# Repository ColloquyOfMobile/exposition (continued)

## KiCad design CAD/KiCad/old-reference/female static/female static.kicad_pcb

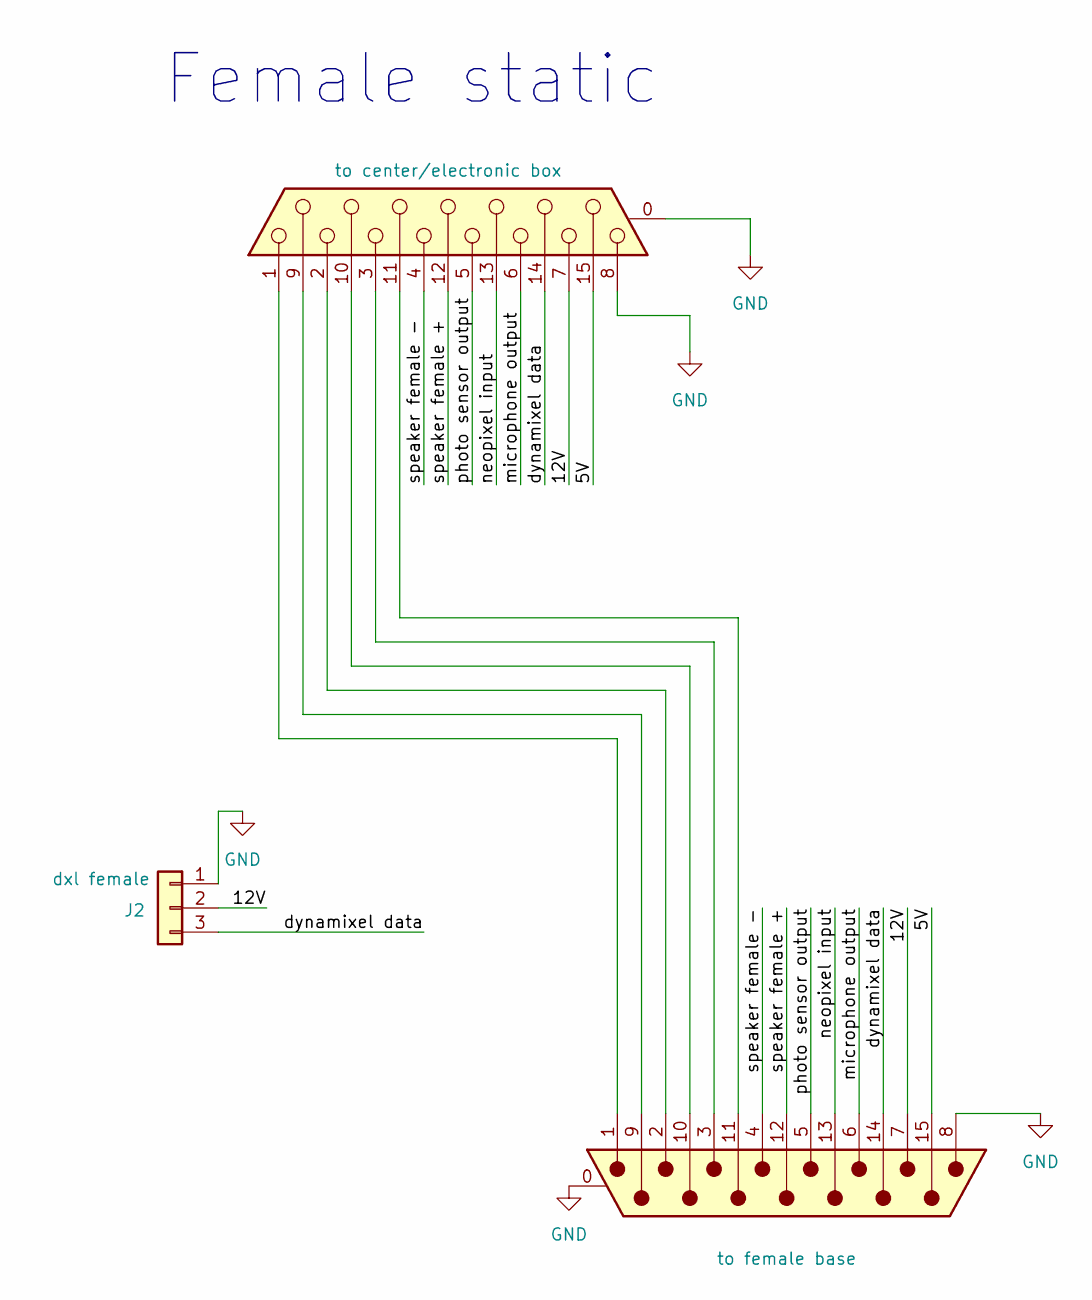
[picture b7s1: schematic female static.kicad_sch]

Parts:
J1: to center/electronic box; DSUB-15_Female_Horizontal_P2.77x2.84mm_EdgePinOffset4.94mm_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
J2: dxl female; JST_EH_B3B-EH-A_1x03_P2.50mm_Vertical
J3: to female base; DSUB-15_Male_Horizontal_P2.77x2.84mm_EdgePinOffset4.94mm_Ho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

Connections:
/5V: J1.15, J3.15
/12V: J1.7, J2.2, J3.7
/dynamixel data: J1.14, J2.3, J3.14
/microphone output: J1.6, J3.6
/neopixel input: J1.13, J3.13
/photo sensor output: J1.5, J3.5
/speaker female +: J1.12, J3.12
/speaker female -: J1.4, J3.4
GND: J1.0 (PAD), J1.8, J2.1, J3.0 (PAD), J3.8
unnamed: J1.9, J3.9
unnamed: J1.10, J3.10
unnamed: J1.11 (P111), J3.11 (P111)
unnamed: J1.1, J3.1
unnamed: J1.2, J3.2
unnamed: J1.3, J3.3

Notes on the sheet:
Female static

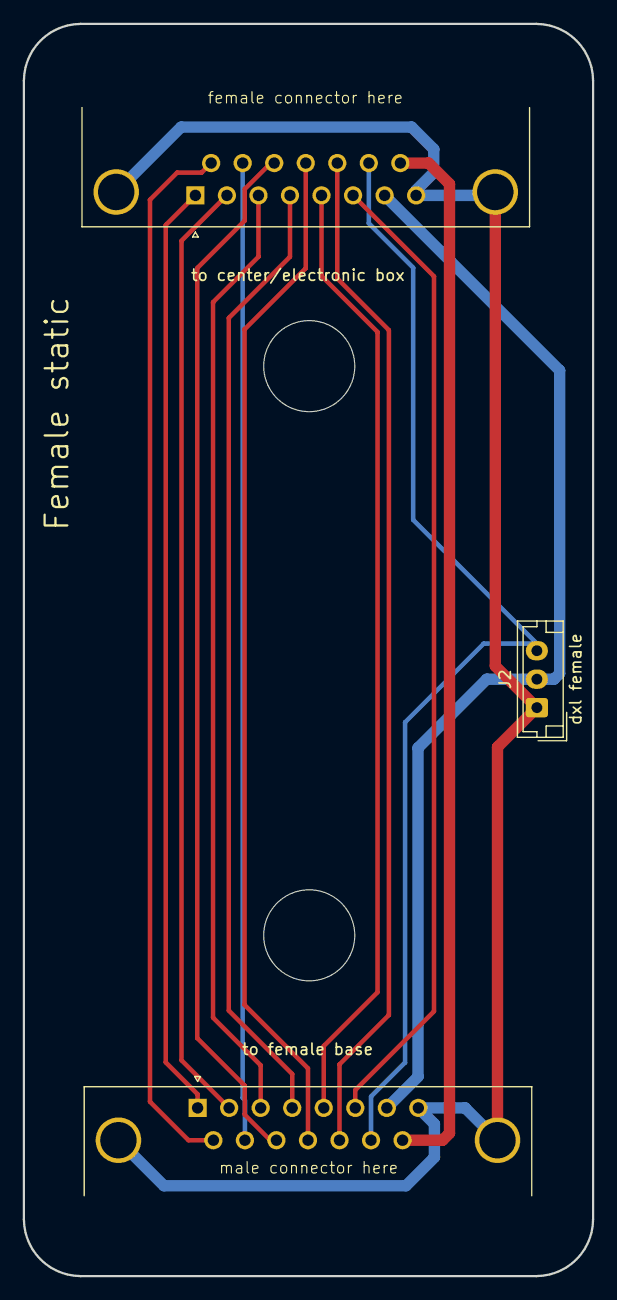
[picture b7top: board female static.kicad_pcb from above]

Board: 2 copper layers, 50.0 x 110.0 mm, 3 parts (0 on the bottom side), 15 nets.

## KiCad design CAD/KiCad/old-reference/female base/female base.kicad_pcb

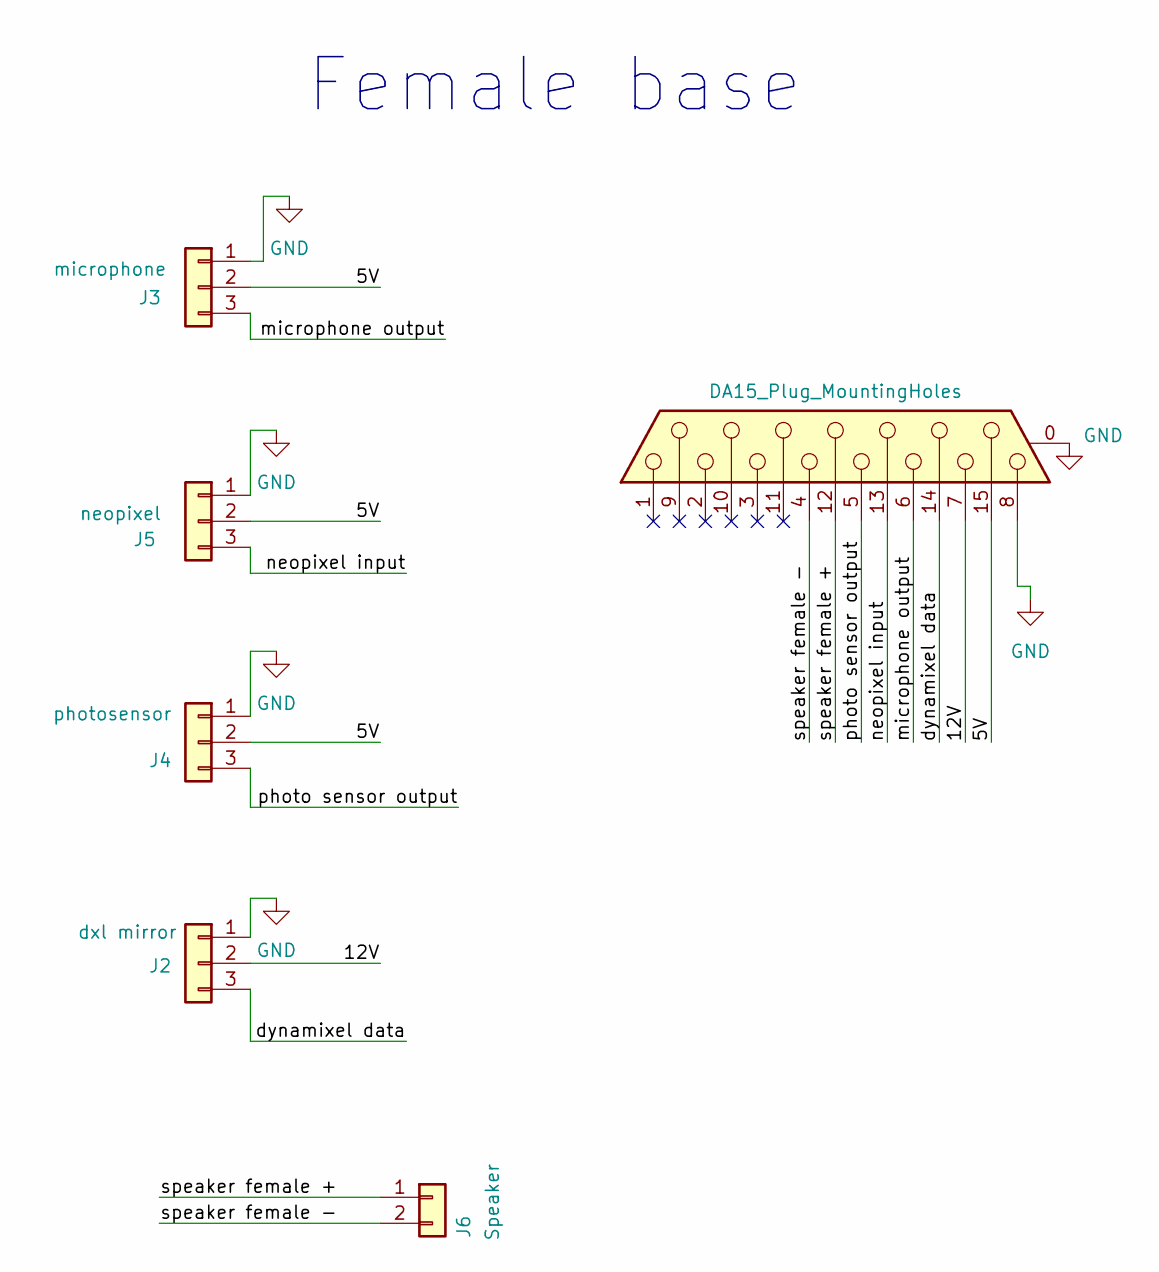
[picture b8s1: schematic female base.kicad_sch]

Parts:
J2: dxl mirror; JST_EH_B3B-EH-A_1x03_P2.50mm_Vertical
J3: microphone; JST_EH_B3B-EH-A_1x03_P2.50mm_Vertical
J4: photosensor; JST_EH_B3B-EH-A_1x03_P2.50mm_Vertical
J5: neopixel; JST_EH_B3B-EH-A_1x03_P2.50mm_Vertical
J6: Speaker; JST_EH_B2B-EH-A_1x02_P2.50mm_Vertical
J7: DA15_Plug_MountingHoles; DSUB-15_Female_Horizontal_P2.77x2.84mm_EdgePinOffset4.94mm_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

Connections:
/5V: J3.2, J4.2, J5.2, J7.15
/12V: J2.2, J7.7
/dynamixel data: J2.3, J7.14
/microphone output: J3.3, J7.6
/neopixel input: J5.3, J7.13
/photo sensor output: J4.3, J7.5
/speaker female +: J6.1, J7.12
/speaker female -: J6.2, J7.4
GND: J2.1, J3.1, J4.1, J5.1, J7.0 (PAD), J7.8

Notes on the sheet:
Female base

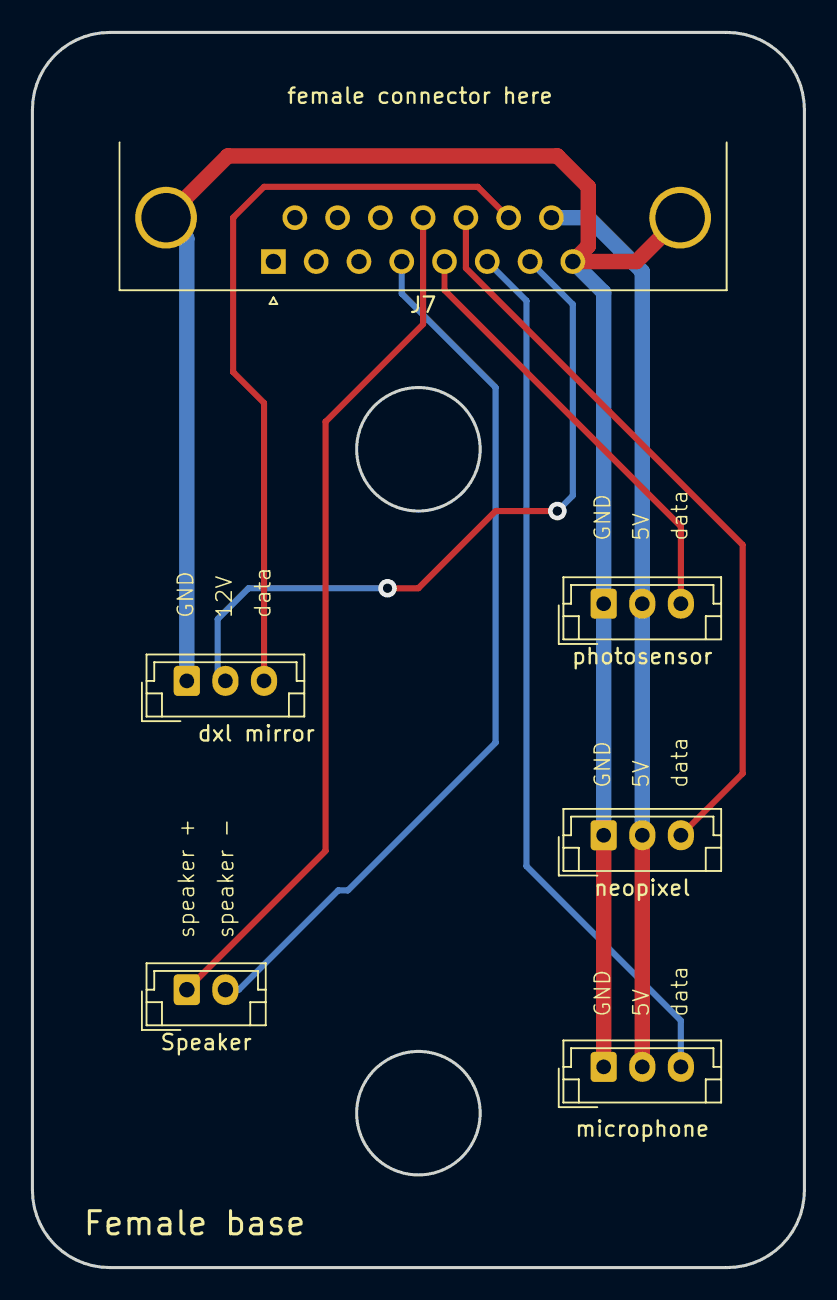
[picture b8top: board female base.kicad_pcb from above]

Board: 2 copper layers, 50.0 x 80.0 mm, 6 parts (0 on the bottom side), 9 nets.

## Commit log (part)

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2026-06-30 plot threashold
